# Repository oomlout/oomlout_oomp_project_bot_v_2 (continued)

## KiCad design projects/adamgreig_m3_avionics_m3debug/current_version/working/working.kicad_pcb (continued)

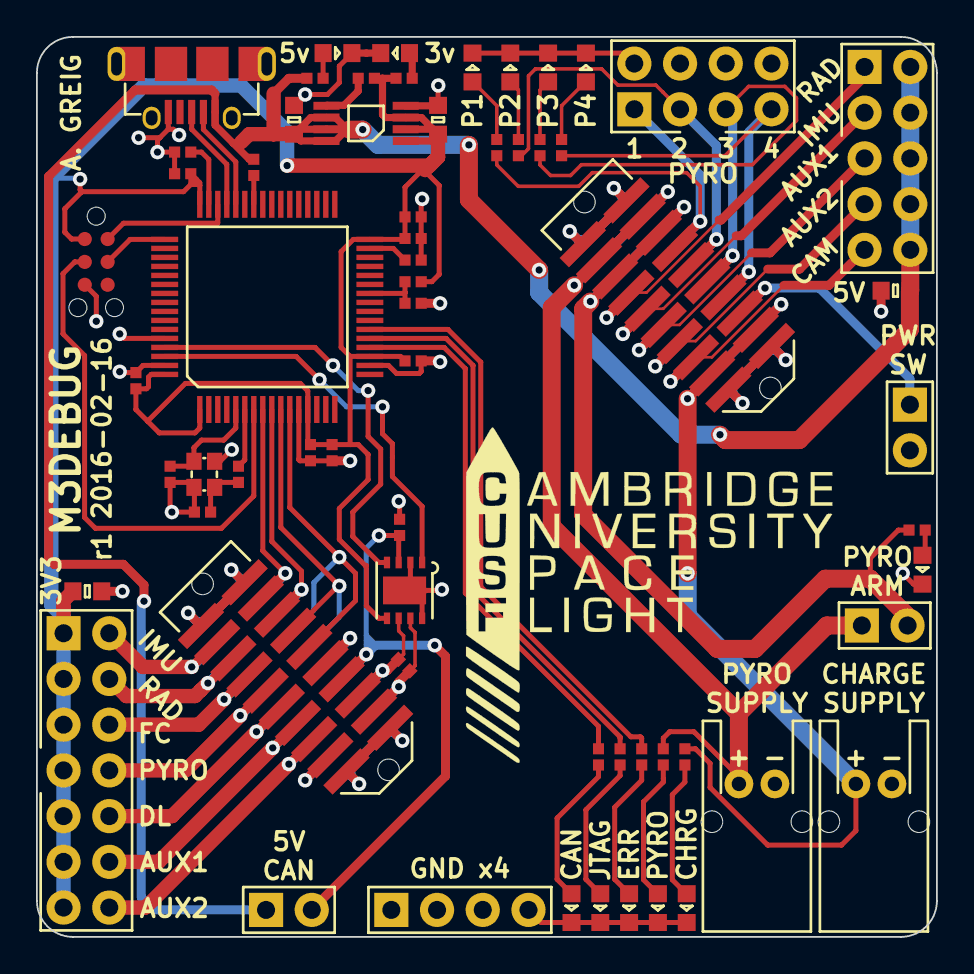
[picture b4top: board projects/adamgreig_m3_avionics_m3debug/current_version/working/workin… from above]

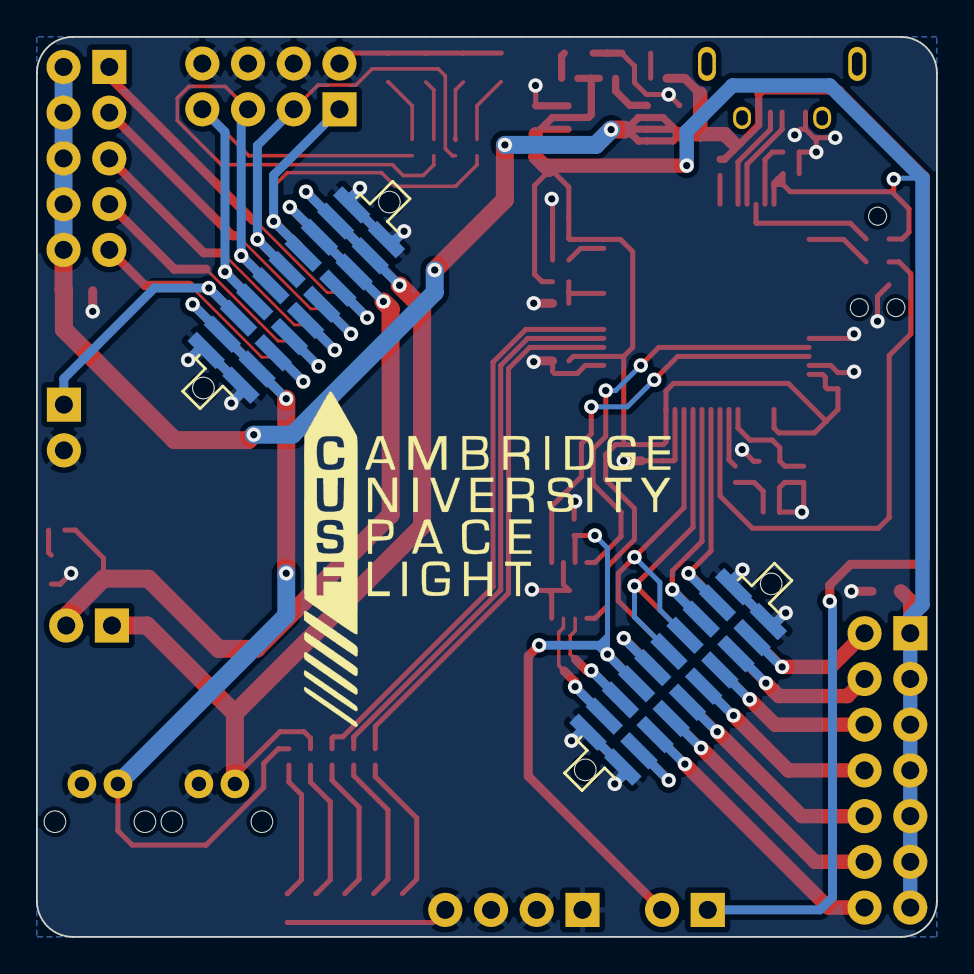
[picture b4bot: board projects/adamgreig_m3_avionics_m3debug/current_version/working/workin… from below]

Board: 2 copper layers, 50.0 x 50.0 mm, 65 parts (2 on the bottom side), 62 nets.

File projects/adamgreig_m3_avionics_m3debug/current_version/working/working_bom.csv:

"Id";"Designator";"Footprint";"Quantity";"Designation";"Supplier and ref";
1;"C1,C2";"0402";2;"10p";;;
2;"C3";"0402";1;"4µ7";;;
3;"C4,C5,C7,C8,C9,C12";"0402";6;"100n";;;
4;"C6";"0402";1;"1µ";;;
5;"C10,C11";"0402";2;"2µ2";;;
6;"C13,C15";"0603";2;"2µ2";;;
7;"C14";"0402";1;"1n";;;
8;"C16,C17";"0603";2;"10µ";;;
9;"D1,D2";"0603-LED";2;"YLW";;;
10;"D3,D4,D5,D6,D7,D8";"0603-LED";6;"RED";;;
11;"D9,D10,D11,D12";"0603-LED";4;"GRN";;;
12;"IC1";"LQFP-64";1;"STM32F405RxTx";;;
13;"IC2";"DFN-8-EP-MICROCHIP";1;"MCP2562";;;
14;"IC3";"MSOP-8";1;"ADP3335";;;
15;"J1";"TFML-110-02-L-D";1;"WEST TOP";;;
16;"J3";"TFML-110-02-L-D";1;"EAST TOP";;;
17;"J5";"S02B-PASK-2";1;"PYRO_SUPPLY";;;
18;"J6";"DIL-254P-08";1;"PYROS";;;
19;"J8";"S02B-PASK-2";1;"CHARGE";;;
20;"J9";"MICROUSB_MOLEX_47589-0001";1;"MICROUSB";;;
21;"J10";"DIL-254P-10";1;"5V_SUPPLY";;;
22;"J12";"DIL-254P-14";1;"3V3_SUPPLY";;;
23;"P1";"TC2030-NL";1;"SWD_TC";;;
24;"R1,R2,R3,R4,R9,R10,R11,R12,R13,R14,R15,R16,R17";"0402";13;"1k";;;
25;"R5";"0402";1;"100";;;
26;"R6";"0402";1;"120";;;
27;"R7";"0402";1;"4k7";;;
28;"R8";"0402";1;"10k";;;
29;"Y1";"XTAL-20x16";1;"26M";;;
30;"J7";"SIL-254P-02";1;"PYRO_ARM";;;
31;"J11";"SIL-254P-02";1;"CAN_SUPPLY";;;
32;"J13";"SIL-254P-02";1;"PWRSW";;;
33;"J14";"SIL-254P-04";1;"GND";;;
34;"G***,G***";"cusf_logo_full";2;"LOGO";;;
35;"J2";"SFML-110-02-L-D-LC";1;"WEST BOT";;;
36;"J4";"SFML-110-02-L-D-LC";1;"EAST BOT";;;

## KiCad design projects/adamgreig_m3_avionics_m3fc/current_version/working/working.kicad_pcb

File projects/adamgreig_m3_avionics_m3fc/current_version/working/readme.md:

# m3_avionics
 
## summary 
* id: adamgreig_m3_avionics_m3fc
* user: adamgreig
* name: m3_avionics
* board: m3fc
* repo: https://github.com/adamgreig/m3-avionics
* src_file_repo_kicad_pcb: m3fc/pcb/m3fc.kicad_pcb
* src_file_repo_kicad_pcb_link: https://github.com/adamgreig/m3-avionics/tree/master/m3fc/pcb/m3fc.kicad_pcb

* src_file_repo_sch: m3fc/pcb/m3fc.sch
* src_file_repo_sch_link: https://github.com/adamgreig/m3-avionics/tree/master/m3fc/pcb/m3fc.sch
* full details link: https://github.com/oomlout/oomlout_oomp_project_bot_v_2/tree/main/projects/adamgreig_m3_avionics_m3fc/current_version/working  

## schematic  
  
[schematic (pdf)](working_schematic.pdf) 

## pcb  

[board (pdf)](working.pdf)  

## working_bom
| Id | Designator | Footprint | Quantity | Designation | Supplier and ref |  | None | 
| --- | --- | --- | --- | --- | --- | --- | --- | 
| 1 | C15,C14,C16,C17,C3,C4,C7,C8,C9 | 0402 | 9 | 100n |  |  | [''] | 
| 2 | C13 | 0603 | 1 | 10Âµ |  |  | [''] | 
| 3 | D1 | 0603-LED | 1 | RED |  |  | [''] | 
| 4 | D2 | 0603-LED | 1 | YLW |  |  | [''] | 
| 5 | D3 | 0603-LED | 1 | GRN |  |  | [''] | 
| 6 | IC3 | DFN-8-EP-MICROCHIP | 1 | MCP2562 |  |  | [''] | 
| 7 | IC4 | ADXL3x5 | 1 | ADXL345 |  |  | [''] | 
| 8 | IC2 | MS5611 | 1 | MS5611-01BA03 |  |  | [''] | 
| 9 | P1 | TC2030-NL | 1 | SWD_TC |  |  | [''] | 
| 10 | Q1 | SOT-23 | 1 | NFET |  |  | [''] | 
| 11 | R1,R2,R3,R4,R5 | 0402 | 5 | 100 |  |  | [''] | 
| 12 | J3 | TFML-110-02-L-D | 1 | EAST TOP |  |  | [''] | 
| 13 | C1,C6 | 0402 | 2 | 10p |  |  | [''] | 
| 14 | C5 | 0402 | 1 | 1Âµ |  |  | [''] | 
| 15 | IC1 | LQFP-64 | 1 | STM32F405RxTx |  |  | [''] | 
| 16 | J1 | TFML-110-02-L-D | 1 | WEST TOP |  |  | [''] | 
| 17 | Y1 | XTAL-20x16 | 1 | 26M |  |  | [''] | 
| 18 | LS1 | KSSG13J12-N | 1 | SOUNDER |  |  | [''] | 
| 19 | C2 | 0402 | 1 | 4Âµ7 |  |  | [''] | 
| 20 | C10,C11 | 0402 | 2 | 2Âµ2 |  |  | [''] | 
| 21 | D4 | SOD-323 | 1 | D |  |  | [''] | 
| 22 | G*** | cusf_logo_small | 1 | LOGO |  |  | [''] | 
| 23 | J4 | SFML-110-02-L-D-LC | 1 | EAST BOT |  |  | [''] | 
| 24 | J2 | SFML-110-02-L-D-LC | 1 | WEST BOT |  |  | [''] | 
| 25 | G*** | cusf_logo_full | 1 | LOGO |  |  | [''] | 

## bom_schematic
| Ref | Qnty | Value | Cmp name | Footprint | Description | Vendor | DNP | 
| --- | --- | --- | --- | --- | --- | --- | --- | 
| C1, C6 | 2 | 10p | C | agg:0402 |  |  |  | 
| C2 | 1 | 4Âµ7 | C | agg:0402 |  |  |  | 
| C3, C4, C7, C8, C9, C14, C15, C16, C17 | 9 | 100n | C | agg:0402 |  |  |  | 
| C5 | 1 | 1Âµ | C | agg:0402 |  |  |  | 
| C10, C11 | 2 | 2Âµ2 | C | agg:0402 |  |  |  | 
| C13 | 1 | 10Âµ | C | agg:0603 |  |  |  | 
| D1 | 1 | RED | LED | agg:0603-LED |  |  |  | 
| D2 | 1 | YLW | LED | agg:0603-LED |  |  |  | 
| D3 | 1 | GRN | LED | agg:0603-LED |  |  |  | 
| D4 | 1 | D | D | agg:SOD-323 |  |  |  | 
| IC1 | 1 | STM32F405RxTx | STM32F405RxTx | agg:LQFP-64 |  |  |  | 
| IC2 | 1 | MS5611-01BA03 | MS5611-01BA03 | agg:MS5611 |  |  |  | 
| IC3 | 1 | MCP2562 | MCP2562 | agg:DFN-8-EP-MICROCHIP |  |  |  | 
| IC4 | 1 | ADXL345 | ADXL345 | agg:ADXL3x5 |  |  |  | 
| J1 | 1 | WEST TOP | CONN_02x10 | agg:TFML-110-02-L-D |  |  |  | 
| J2 | 1 | WEST BOT | CONN_02x10 | agg:SFML-110-02-L-D-LC |  |  |  | 
| J3 | 1 | EAST TOP | CONN_02x10 | agg:TFML-110-02-L-D |  |  |  | 
| J4 | 1 | EAST BOT | CONN_02x10 | agg:SFML-110-02-L-D-LC |  |  |  | 
| LS1 | 1 | SOUNDER | SOUNDER | agg:KSSG13J12-N |  |  |  | 
| P1 | 1 | SWD_TC | SWD_TC | agg:TC2030-NL |  |  |  | 
| Q1 | 1 | NFET | NFET | agg:SOT-23 |  |  |  | 
| R1, R2, R3, R4, R5 | 5 | 100 | R | agg:0402 |  |  |  | 
| Y1 | 1 | 26M | SMD_XTAL | agg:XTAL-20x16 |  |  |  |

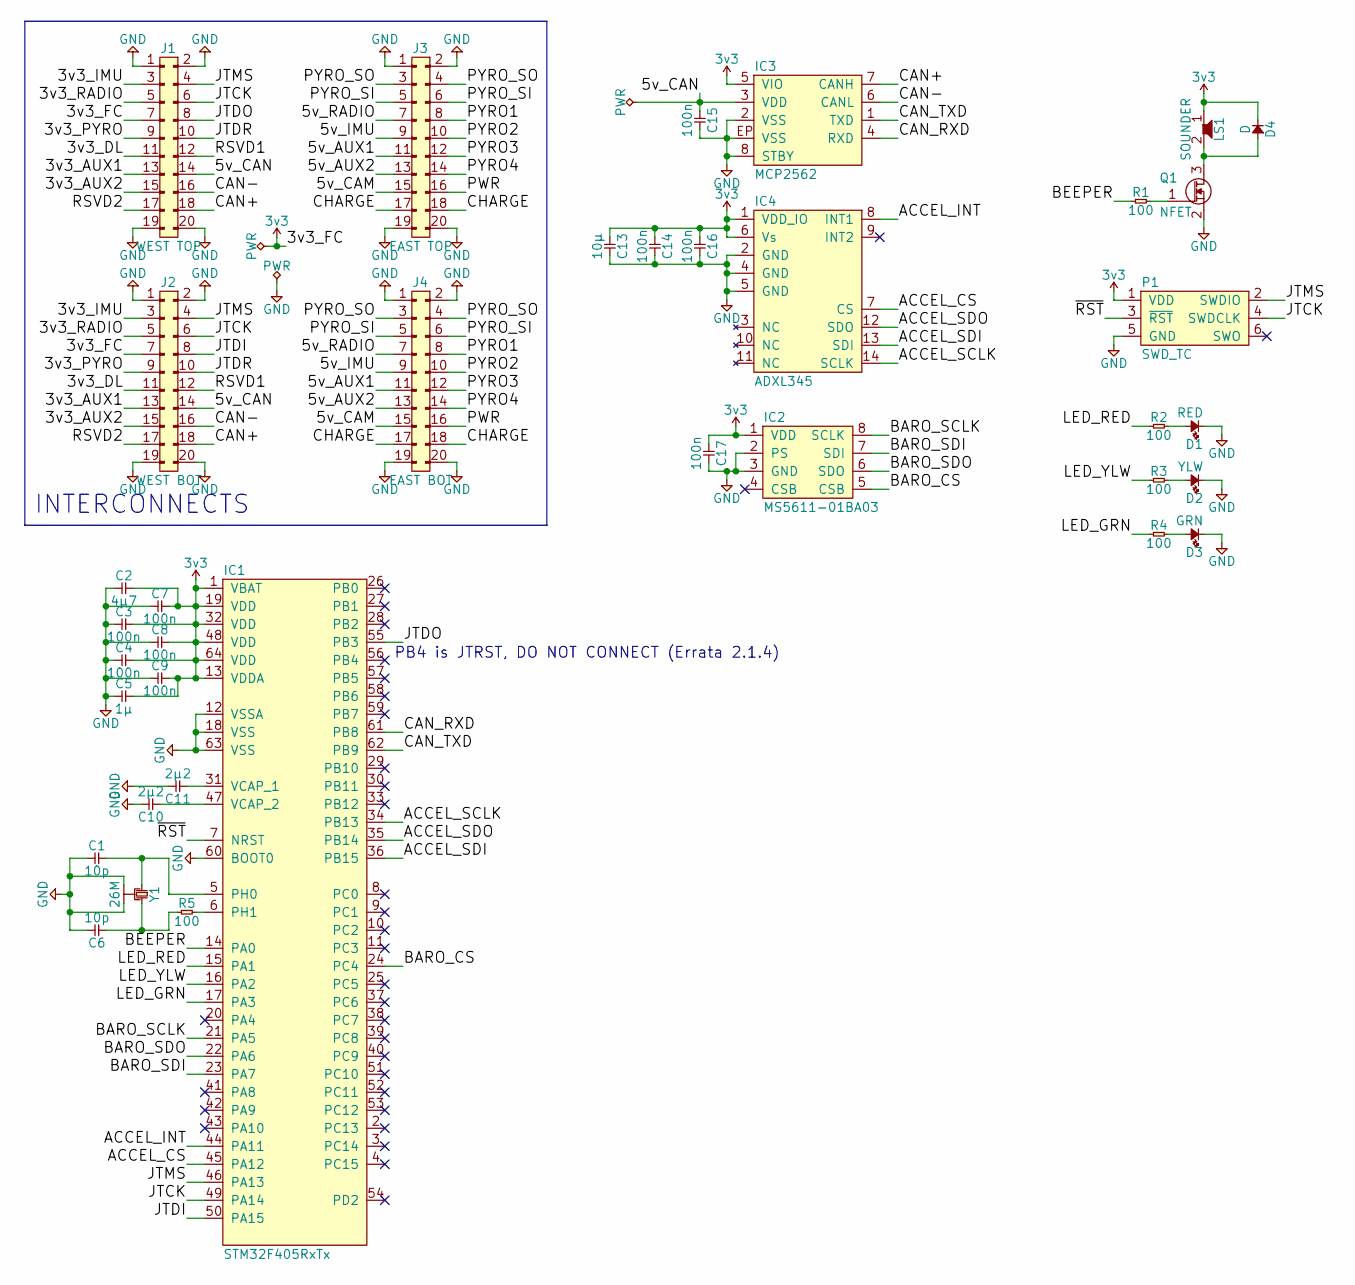
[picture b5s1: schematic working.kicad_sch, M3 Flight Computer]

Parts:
C1, C6: 10p; 0402; Farnell 2496790
C2: 4µ7; 0402; Farnell 2426952
C3, C4, C7, C8, C9, C14, C15, C16, C17: 100n; 0402; Farnell 2496771
C5: 1µ; 0402; Farnell 2496814
C10, C11: 2µ2; 0402; Farnell 2362088
C13: 10µ; 0603; Farnell 2456110
D1: RED; 0603-LED; Farnell 2314404
D2: YLW; 0603-LED; Farnell 2335804
D3: GRN; 0603-LED; Farnell 2290363
D4: D; SOD-323; Farnell 1459033
IC1: STM32F405RxTx; LQFP-64; Farnell 2064363
IC2: MS5611-01BA03; MS5611; Farnell 2362662
IC3: MCP2562; DFN-8-EP-MICROCHIP; Farnell 2448755
IC4: ADXL345; ADXL3x5; Farnell 1853935
J1: WEST TOP; TFML-110-02-L-D
J2: WEST BOT; SFML-110-02-L-D-LC
J3: EAST TOP; TFML-110-02-L-D
J4: EAST BOT; SFML-110-02-L-D-LC
LS1: SOUNDER; KSSG13J12-N; Farnell 2215089
P1: SWD_TC; TC2030-NL
Q1: NFET; SOT-23; Farnell 2069541
R1, R2, R3, R4, R5: 100; 0402; Farnell 9239111
Y1: 26M; XTAL-20x16; Farnell 2506952

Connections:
3v3: C2.2, C3.2, C4.2, C5.2, C7.2, C8.2, C9.2, C13.1, C14.1, C16.1, C17.1, D4.1, IC1.1 (VBAT), IC1.13 (VDDA), IC1.19 (VDD), IC1.32 (VDD), IC1.48 (VDD), IC1.64 (VDD), IC2.1 (VDD), IC3.5 (VIO), IC4.1 (VDD_IO), IC4.6 (Vs), J1.7, J2.7, LS1.1, P1.1 (VDD)
/3v3_AUX1: J1.13, J2.13
/3v3_AUX2: J1.15, J2.15
/3v3_DL: J1.11, J2.11
/3v3_IMU: J1.3, J2.3
/3v3_PYRO: J1.9, J2.9
/3v3_RADIO: J1.5, J2.5
/5v_AUX1: J3.11, J4.11
/5v_AUX2: J3.13, J4.13
/5v_CAM: J3.15, J4.15
/5v_CAN: C15.1, IC3.3 (VDD), J1.14, J2.14
/5v_IMU: J3.9, J4.9
/5v_RADIO: J3.7, J4.7
/ACCEL_CS: IC1.45 (PA12), IC4.7 (CS)
/ACCEL_INT: IC1.44 (PA11), IC4.8 (INT1)
/ACCEL_SCLK: IC1.34 (PB13), IC4.14 (SCLK)
/ACCEL_SDI: IC1.36 (PB15), IC4.13 (SDI)
/ACCEL_SDO: IC1.35 (PB14), IC4.12 (SDO)
/BARO_CS: IC1.24 (PC4), IC2.5 (CSB)
/BARO_SCLK: IC1.21 (PA5), IC2.8 (SCLK)
/BARO_SDI: IC1.23 (PA7), IC2.7 (SDI)
/BARO_SDO: IC1.22 (PA6), IC2.6 (SDO)
/BEEPER: IC1.14 (PA0), R1.1
/CAN+: IC3.7 (CANH), J1.18, J2.18
/CAN-: IC3.6 (CANL), J1.16, J2.16
/CAN_RXD: IC1.61 (PB8), IC3.4 (RXD)
/CAN_TXD: IC1.62 (PB9), IC3.1 (TXD)
/CHARGE: J3.17, J3.18, J4.17, J4.18
/JTCK: IC1.49 (PA14), J1.6, J2.6, P1.4 (SWDCLK)
/JTDI: IC1.50 (PA15), J2.8
/JTDO: IC1.55 (PB3), J1.8
/JTDR: J1.10, J2.10
/JTMS: IC1.46 (PA13), J1.4, J2.4, P1.2 (SWDIO)
/LED_GRN: IC1.17 (PA3), R4.1
/LED_RED: IC1.15 (PA1), R2.1
/LED_YLW: IC1.16 (PA2), R3.1
/PWR: J3.16, J4.16
/PYRO1: J3.8, J4.8
/PYRO2: J3.10, J4.10
/PYRO3: J3.12, J4.12
/PYRO4: J3.14, J4.14
/PYRO_SI: J3.5, J3.6, J4.5, J4.6
/PYRO_SO: J3.3, J3.4, J4.3, J4.4
/RSVD1: J1.12, J2.12
/RSVD2: J1.17, J2.17
/~RST: IC1.7 (NRST), P1.3 (~RST)
GND: C1.1, C2.1, C3.1, C4.1, C5.1, C6.2, C7.1, C8.1, C9.1, C10.2, C11.2, C13.2, C14.2, C15.2, C16.2, C17.2, D1.1, D2.1, D3.1, IC1.12 (VSSA), IC1.18 (VSS), IC1.60 (BOOT0), IC1.63 (VSS), IC2.2 (PS), IC2.3 (GND), IC3.2 (VSS), IC3.8 (STBY), IC3.EP (VSS), IC4.2 (GND), IC4.4 (GND), IC4.5 (GND), J1.1, J1.2, J1.19, J1.20, J2.1, J2.2, J2.19, J2.20, J3.1, J3.2, J3.19, J3.20, J4.1, J4.2, J4.19, J4.20, P1.5 (GND), Q1.2 (S), Y1.2, Y1.4
unnamed: C1.2, IC1.5 (PH0), Y1.1
unnamed: C6.1, R5.1, Y1.3
unnamed: C10.1, IC1.47 (VCAP_2)
unnamed: C11.1, IC1.31 (VCAP_1)
unnamed: D1.2, R2.2
unnamed: D2.2, R3.2
unnamed: D3.2, R4.2
unnamed: D4.2, LS1.2, Q1.3 (D)
unnamed: IC1.6 (PH1), R5.2
unnamed: Q1.1 (G), R1.2

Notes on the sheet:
PB4 is JTRST, DO NOT CONNECT (Errata 2.1.4)
INTERCONNECTS

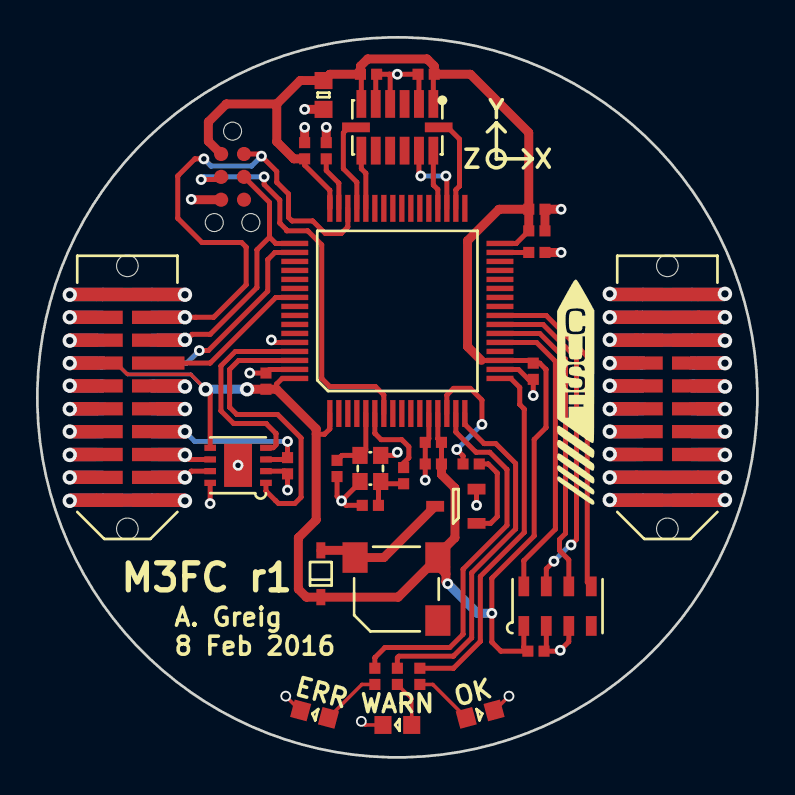
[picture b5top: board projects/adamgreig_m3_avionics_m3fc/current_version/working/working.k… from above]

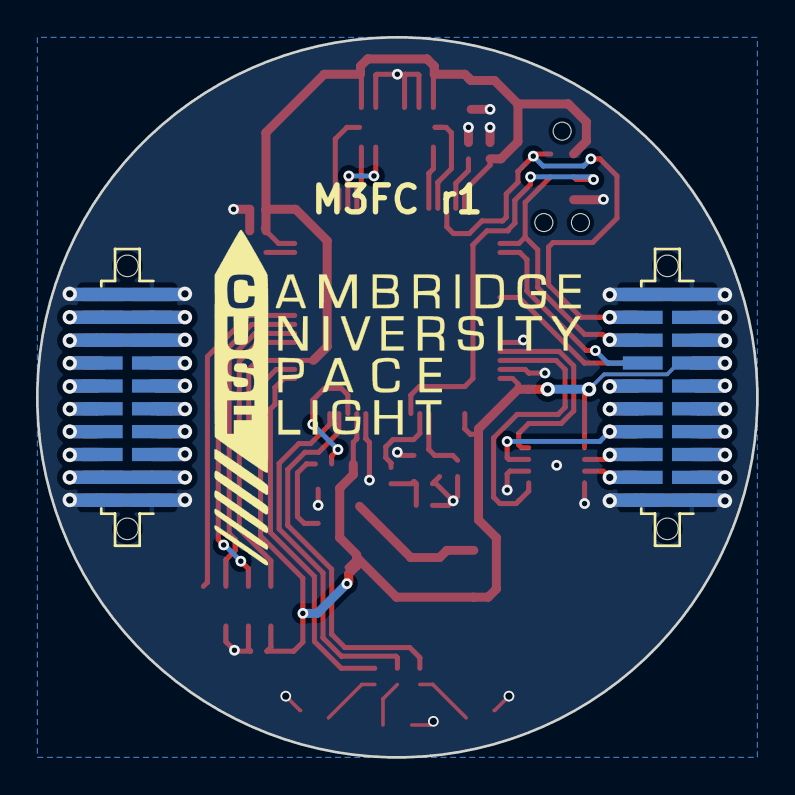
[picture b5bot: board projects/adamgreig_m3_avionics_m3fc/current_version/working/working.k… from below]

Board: 2 copper layers, 40.0 x 40.0 mm, 37 parts (2 on the bottom side), 57 nets.

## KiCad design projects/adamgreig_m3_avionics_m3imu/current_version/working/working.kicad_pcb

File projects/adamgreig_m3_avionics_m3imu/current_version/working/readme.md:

# m3_avionics
 
## summary 
* id: adamgreig_m3_avionics_m3imu
* user: adamgreig
* name: m3_avionics
* board: m3imu
* repo: https://github.com/adamgreig/m3-avionics
* src_file_repo_kicad_pcb: m3imu/pcb/m3imu.kicad_pcb
* src_file_repo_kicad_pcb_link: https://github.com/adamgreig/m3-avionics/tree/master/m3imu/pcb/m3imu.kicad_pcb

* src_file_repo_sch: m3imu/pcb/m3imu.sch
* src_file_repo_sch_link: https://github.com/adamgreig/m3-avionics/tree/master/m3imu/pcb/m3imu.sch
* full details link: https://github.com/oomlout/oomlout_oomp_project_bot_v_2/tree/main/projects/adamgreig_m3_avionics_m3imu/current_version/working  

## schematic  
  
[schematic (pdf)](working_schematic.pdf) 

## pcb  

[board (pdf)](working.pdf)  

## working_bom
| Id | Designator | Footprint | Quantity | Designation | Supplier and ref |  | None | 
| --- | --- | --- | --- | --- | --- | --- | --- | 
| 1 | C1,C2 | 0402 | 2 | 10p |  |  | [''] | 
| 2 | C3 | 0402 | 1 | 4Âµ7 |  |  | [''] | 
| 3 | C4,C5,C7,C8,C9,C12,C13,C15,C16,C17 | 0402 | 10 | 100n |  |  | [''] | 
| 4 | C6 | 0402 | 1 | 1Âµ |  |  | [''] | 
| 5 | C10,C11 | 0402 | 2 | 2Âµ2 |  |  | [''] | 
| 6 | C14 | 0402 | 1 | 10n |  |  | [''] | 
| 7 | D1 | 0603-LED | 1 | RED |  |  | [''] | 
| 8 | D3 | 0603-LED | 1 | GRN |  |  | [''] | 
| 9 | IC1 | LQFP-64 | 1 | STM32F405RxTx |  |  | [''] | 
| 10 | IC2 | DFN-8-EP-MICROCHIP | 1 | MCP2562 |  |  | [''] | 
| 11 | IC3 | MS5611 | 1 | MS5611-01BA03 |  |  | [''] | 
| 12 | IC4 | QFN-24-MPU9250 | 1 | MPU-9250 |  |  | [''] | 
| 13 | R1,R2,R4 | 0402 | 3 | 100 |  |  | [''] | 
| 14 | Y1 | XTAL-20x16 | 1 | 26M |  |  | [''] | 
| 15 | X1 | cusf_logo_small | 1 | PART |  |  | [''] | 
| 16 | J1 | MICROUSB_MOLEX_47589-0001 | 1 | MICROUSB |  |  | [''] | 
| 17 | D2 | SOT-666 | 1 | USBLC6-2P6 |  |  | [''] | 
| 18 | R3,R6,R7,R8,R9 | 0603 | 5 | 47K |  |  | [''] | 
| 19 | J3 | TFML-110-02-L-D | 1 | WEST TOP |  |  | [''] | 
| 20 | J5 | TFML-110-02-L-D | 1 | EAST TOP |  |  | [''] | 
| 21 | J2 | SFML-110-02-L-D-LC | 1 | WEST BOT |  |  | [''] | 
| 22 | J4 | SFML-110-02-L-D-LC | 1 | EAST BOT |  |  | [''] | 
| 23 | U2 | MICROSD_MOLEX_503398-1892 | 1 | MICROSD-RESCUE-main |  |  | [''] | 

## bom_schematic
| Ref | Qnty | Value | Cmp name | Footprint | Description | Vendor | DNP | 
| --- | --- | --- | --- | --- | --- | --- | --- | 
| C1, C2 | 2 | 10p | C | agg:0402 |  |  |  | 
| C3 | 1 | 4Âµ7 | C | agg:0402 |  |  |  | 
| C4, C5, C7, C8, C9, C12, C13, C15, C16, C17 | 10 | 100n | C | agg:0402 |  |  |  | 
| C6 | 1 | 1Âµ | C | agg:0402 |  |  |  | 
| C10, C11 | 2 | 2Âµ2 | C | agg:0402 |  |  |  | 
| C14 | 1 | 10n | C | agg:0402 |  |  |  | 
| D1 | 1 | RED | LED | agg:0603-LED |  |  |  | 
| D2 | 1 | USBLC6-2P6 | USBLC6-2P6 | agg:SOT-666 |  |  |  | 
| D3 | 1 | GRN | LED | agg:0603-LED |  |  |  | 
| IC1 | 1 | STM32F405RxTx | STM32F405RxTx | agg:LQFP-64 |  |  |  | 
| IC2 | 1 | MCP2562 | MCP2562 | agg:DFN-8-EP-MICROCHIP |  |  |  | 
| IC3 | 1 | MS5611-01BA03 | MS5611-01BA03 | agg:MS5611 |  |  |  | 
| IC4 | 1 | MPU-9250 | MPU-9250 | agg:QFN-24-MPU9250 |  |  |  | 
| J1 | 1 | MICROUSB | MICROUSB | agg:MICROUSB_MOLEX_47589-0001 |  |  |  | 
| J2 | 1 | WEST BOT | CONN_02x10 | agg:SFML-110-02-L-D-LC |  |  |  | 
| J3 | 1 | WEST TOP | CONN_02x10 | agg:TFML-110-02-L-D |  |  |  | 
| J4 | 1 | EAST BOT | CONN_02x10 | agg:SFML-110-02-L-D-LC |  |  |  | 
| J5 | 1 | EAST TOP | CONN_02x10 | agg:TFML-110-02-L-D |  |  |  | 
| R1, R2, R4 | 3 | 100 | R | agg:0402 |  |  |  | 
| R3, R6, R7, R8, R9 | 5 | 47K | R | agg:0603 |  |  |  | 
| U2 | 1 | MICROSD-RESCUE-main | MICROSD-RESCUE-main | agg:MICROSD_MOLEX_503398-1892 |  |  |  | 
| X1 | 1 | PART | PART | M3_IMU:cusf_logo_small |  |  |  | 
| Y1 | 1 | 26M | SMD_XTAL | agg:XTAL-20x16 |  |  |  |

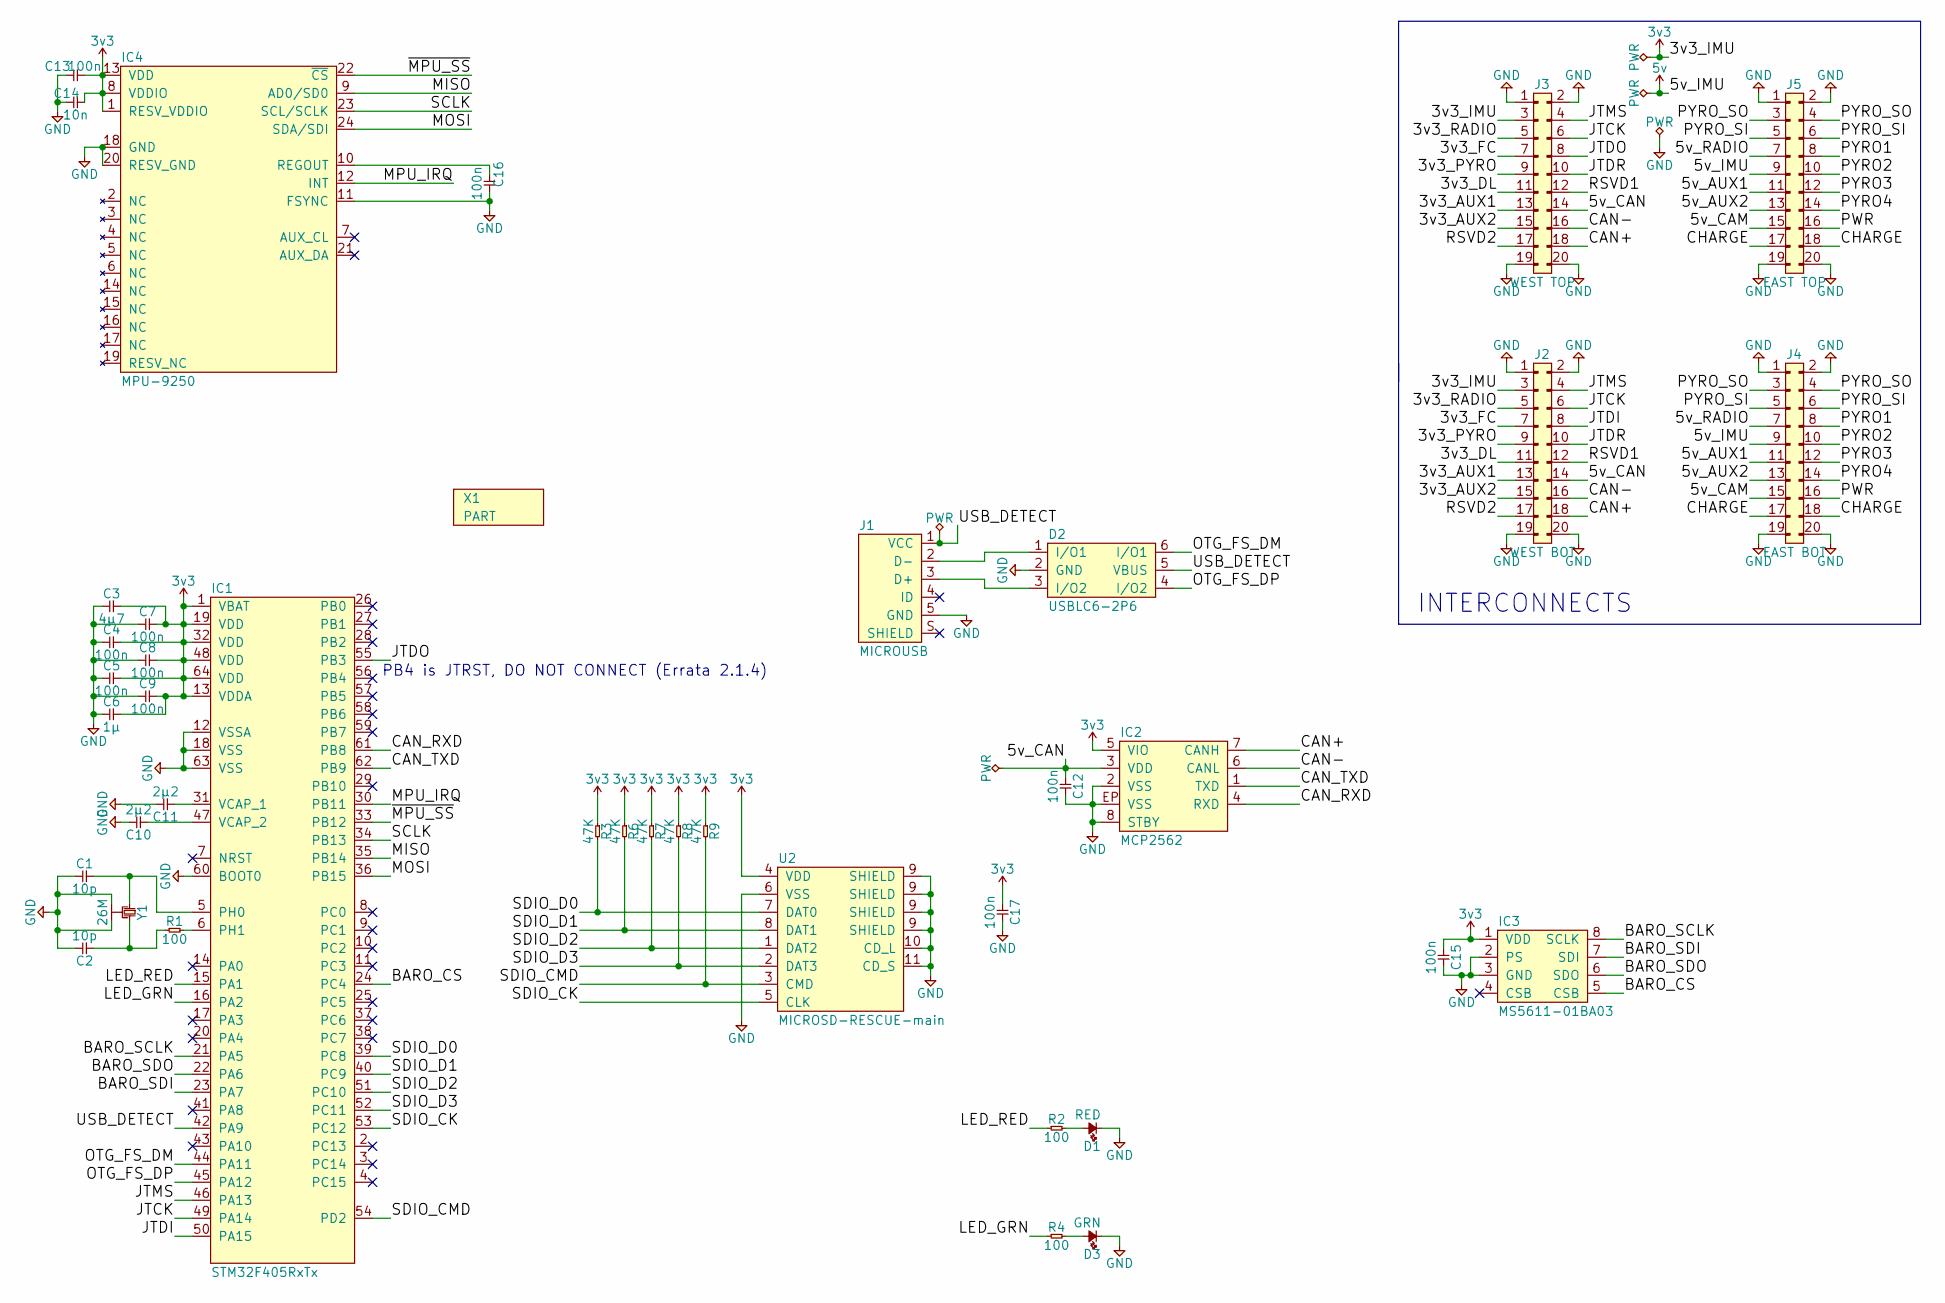
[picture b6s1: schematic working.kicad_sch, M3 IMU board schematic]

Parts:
C1, C2: 10p; 0402; Farnell 2496790
C3: 4µ7; 0402; Farnell 2426952
C4, C5, C7, C8, C9, C12, C13, C15, C16, C17: 100n; 0402; Farnell 2496771
C6: 1µ; 0402; Farnell 2496814
C10, C11: 2µ2; 0402; Farnell 2362088
C14: 10n; 0402; Farnell 1414575
D1: RED; 0603-LED; Farnell 2314404
D2: USBLC6-2P6; SOT-666; Farnell 1295310
D3: GRN; 0603-LED; Farnell 2290363
IC1: STM32F405RxTx; LQFP-64; Farnell 2064363
IC2: MCP2562; DFN-8-EP-MICROCHIP; Farnell 2448755
IC3: MS5611-01BA03; MS5611; Farnell 2362662
IC4: MPU-9250; QFN-24-MPU9250; DigiKey 1428-1019-1-ND
J1: MICROUSB; MICROUSB_MOLEX_47589-0001; Farnell 1568023
J2: WEST BOT; SFML-110-02-L-D-LC
J3: WEST TOP; TFML-110-02-L-D
J4: EAST BOT; SFML-110-02-L-D-LC
J5: EAST TOP; TFML-110-02-L-D
R1, R2, R4: 100; 0402; Farnell 9239111
R3, R6, R7, R8, R9: 47K; 0603; Farnell 9238689
U2: MICROSD-RESCUE-main; MICROSD_MOLEX_503398-1892; Farnell 2358234
X1: PART; cusf_logo_small
Y1: 26M; XTAL-20x16; Farnell 2506952

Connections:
3v3: C3.2, C4.2, C5.2, C6.2, C7.2, C8.2, C9.2, C13.2, C14.2, C15.1, C17.1, IC1.1 (VBAT), IC1.13 (VDDA), IC1.19 (VDD), IC1.32 (VDD), IC1.48 (VDD), IC1.64 (VDD), IC2.5 (VIO), IC3.1 (VDD), IC4.1 (RESV_VDDIO), IC4.8 (VDDIO), IC4.13 (VDD), J2.3, J3.3, R3.1, R6.1, R7.1, R8.1, R9.1, U2.4 (VDD)
5v: J4.9, J5.9
/3v3_AUX1: J2.13, J3.13
/3v3_AUX2: J2.15, J3.15
/3v3_DL: J2.11, J3.11
/3v3_FC: J2.7, J3.7
/3v3_PYRO: J2.9, J3.9
/3v3_RADIO: J2.5, J3.5
/5v_AUX1: J4.11, J5.11
/5v_AUX2: J4.13, J5.13
/5v_CAM: J4.15, J5.15
/5v_CAN: C12.1, IC2.3 (VDD), J2.14, J3.14
/5v_RADIO: J4.7, J5.7
/BARO_CS: IC1.24 (PC4), IC3.5 (CSB)
/BARO_SCLK: IC1.21 (PA5), IC3.8 (SCLK)
/BARO_SDI: IC1.23 (PA7), IC3.7 (SDI)
/BARO_SDO: IC1.22 (PA6), IC3.6 (SDO)
/CAN+: IC2.7 (CANH), J2.18, J3.18
/CAN-: IC2.6 (CANL), J2.16, J3.16
/CAN_RXD: IC1.61 (PB8), IC2.4 (RXD)
/CAN_TXD: IC1.62 (PB9), IC2.1 (TXD)
/CHARGE: J4.17, J4.18, J5.17, J5.18
/JTCK: IC1.49 (PA14), J2.6, J3.6
/JTDI: IC1.50 (PA15), J2.8
/JTDO: IC1.55 (PB3), J3.8
/JTDR: J2.10, J3.10
/JTMS: IC1.46 (PA13), J2.4, J3.4
/LED_GRN: IC1.16 (PA2), R4.1
/LED_RED: IC1.15 (PA1), R2.1
/MISO: IC1.35 (PB14), IC4.9 (AD0/SD0)
/MOSI: IC1.36 (PB15), IC4.24 (SDA/SDI)
/MPU_IRQ: IC1.30 (PB11), IC4.12 (INT)
/OTG_FS_DM: D2.6 (I/O1), IC1.44 (PA11)
/OTG_FS_DP: D2.4 (I/O2), IC1.45 (PA12)
/PWR: J4.16, J5.16
/PYRO1: J4.8, J5.8
/PYRO2: J4.10, J5.10
/PYRO3: J4.12, J5.12
/PYRO4: J4.14, J5.14
/PYRO_SI: J4.5, J4.6, J5.5, J5.6
/PYRO_SO: J4.3, J4.4, J5.3, J5.4
/RSVD1: J2.12, J3.12
/RSVD2: J2.17, J3.17
/SCLK: IC1.34 (PB13), IC4.23 (SCL/SCLK)
/SDIO_CK: IC1.53 (PC12), U2.5 (CLK)
/SDIO_CMD: IC1.54 (PD2), R9.2, U2.3 (CMD)
/SDIO_D0: IC1.39 (PC8), R3.2, U2.7 (DAT0)
/SDIO_D1: IC1.40 (PC9), R6.2, U2.8 (DAT1)
/SDIO_D2: IC1.51 (PC10), R7.2, U2.1 (DAT2)
/SDIO_D3: IC1.52 (PC11), R8.2, U2.2 (DAT3)
/USB_DETECT: D2.5 (VBUS), IC1.42 (PA9), J1.1 (VCC)
/~MPU_SS: IC1.33 (PB12), IC4.22 (~CS)
GND: C1.1, C2.2, C3.1, C4.1, C5.1, C6.1, C7.1, C8.1, C9.1, C10.2, C11.2, C12.2, C13.1, C14.1, C15.2, C16.2, C17.2, D1.1, D2.2 (GND), D3.1, IC1.12 (VSSA), IC1.18 (VSS), IC1.60 (BOOT0), IC1.63 (VSS), IC2.2 (VSS), IC2.8 (STBY), IC2.EP (VSS), IC3.2 (PS), IC3.3 (GND), IC4.11 (FSYNC), IC4.18 (GND), IC4.20 (RESV_GND), J1.5 (GND), J2.1, J2.2, J2.19, J2.20, J3.1, J3.2, J3.19, J3.20, J4.1, J4.2, J4.19, J4.20, J5.1, J5.2, J5.19, J5.20, U2.6 (VSS), U2.9 (SHIELD), U2.10 (CD_L), U2.11 (CD_S), Y1.2, Y1.4
unnamed: C1.2, IC1.5 (PH0), Y1.1
unnamed: C2.1, R1.1, Y1.3
unnamed: C10.1, IC1.47 (VCAP_2)
unnamed: C11.1, IC1.31 (VCAP_1)
unnamed: C16.1, IC4.10 (REGOUT)
unnamed: D1.2, R2.2
unnamed: D2.1 (I/O1), J1.2 (D-)
unnamed: D2.3 (I/O2), J1.3 (D+)
unnamed: D3.2, R4.2
unnamed: IC1.6 (PH1), R1.2

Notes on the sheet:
PB4 is JTRST, DO NOT CONNECT (Errata 2.1.4)
INTERCONNECTS

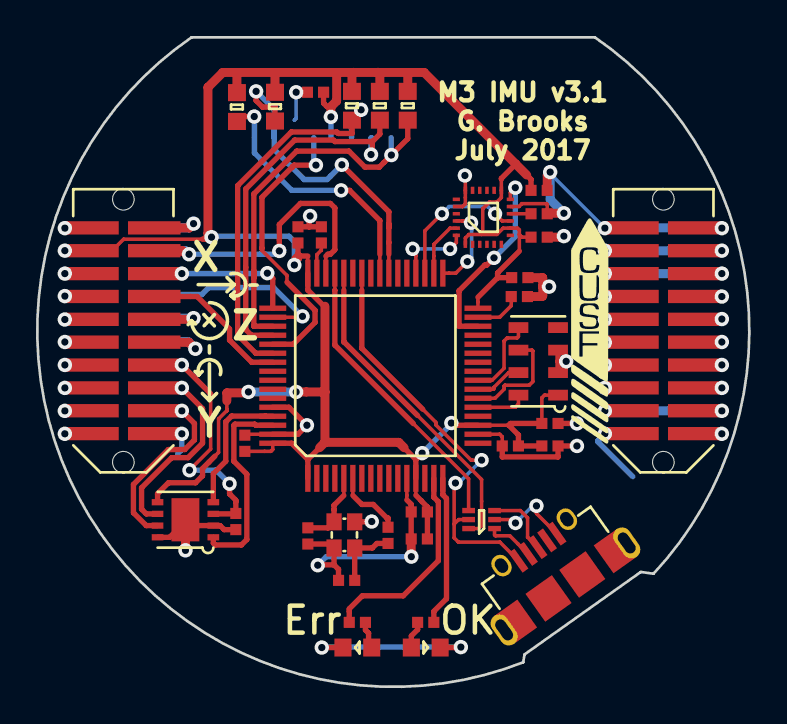
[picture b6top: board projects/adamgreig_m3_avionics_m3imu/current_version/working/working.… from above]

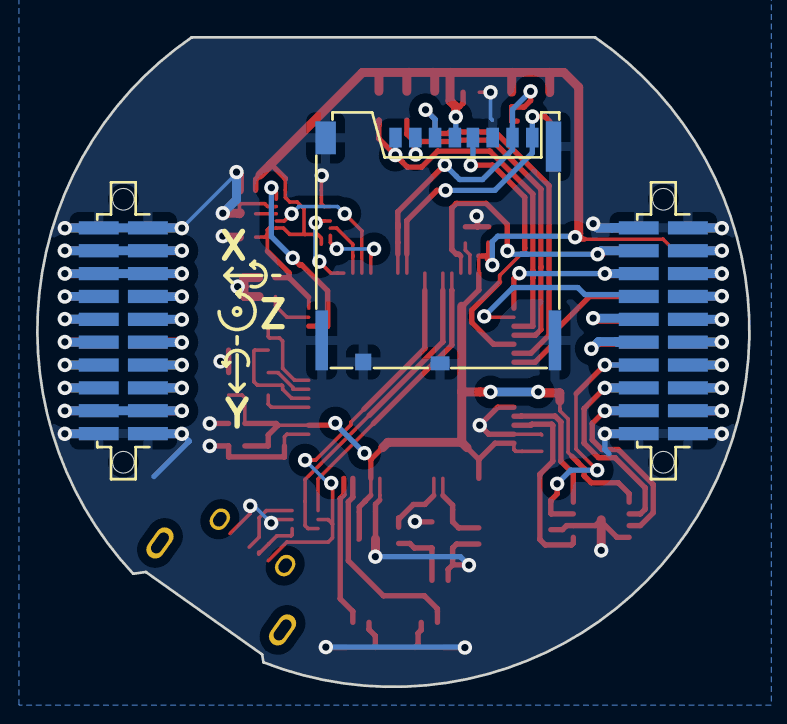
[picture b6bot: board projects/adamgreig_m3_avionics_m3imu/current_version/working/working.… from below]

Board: 2 copper layers, 39.6 x 36.1 mm, 40 parts (3 on the bottom side), 63 nets.
